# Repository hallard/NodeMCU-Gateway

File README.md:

NodeMCU ESP8266 Gateway Goes to WeMos ESP8266
=============================================

This gateway has been updated by a new version for the following reasons:

- Now I'm using [WeMos D1 Mini][9] board instead of NodeMCU's one because they're just smaller and cheaper (you can find them for less than $3). 
- Features remains the same, they got lot of available shields
- USB Serial onboard is CH340 instead of CP210x, and I can upload up to 900Kbps without any issue on windows 10
- I suspect WeMos regulator far better quality than the one used on NodeMCU that are just fake of original AMS117 3V3.
- Just one size version, no error on order are possible!
- Only one drawback, Voltage input on WeMos is limited to 6V and NodeMCU says up to 20V but trust me, I burnt some at only 14V so If I need to power boards with more than 6V I'm using cheap and small DC/DC converters like this [one][20]one. Plenty on ebay. If you need a more serious and robust one, take this amazing [OKI-78SR-5][21] from Murata (up to 36V).

So for all these reasons I switched to WeMos and created same shields than the ones described here, but, due to size constraint I removed some features, you need to be aware that the following ones has been removed on WeMos shields:

- SPI 2.2" or 1.8" TFT LCD connector
- SPI 128x64 OLED connector (I2C one still present)
- Grove I2C connector (but I2C is exposed via OLED connector)
- Lipo Battery connector
- Data connection for any cheap ebay ASK RX receiver
- **New, a push button** has been added to do some UI/Action if needed.

WeMos Gateway shields are located here: 
- Shield for [RFM69W, RFM69HW, RFM12B or RFM69CW][10] with Atmel ATSHA204 for crypto
- Shield for Lora/LoraWan [RFM92, RFM95, RFM96 or RFM98][11] with footprint for Microchip 24AA02E64 64 bits serial number
- **New Shield** for Lora/LoraWAN [Microchip RN2483][12] with footprint for excellent Microchip RN2483 Lora/Lorawan Module

Sorry there is no shield designed for NRF24L01.

If you need NRF24L01 version or if you just want to continue with the NodeMCU gateway you can, this repo is still alive and boards are working fine.

NodeMCU ESP8266 Gateway
=======================

The gateway can host several funny things like

- Socket to plug a NodeMCU V1.0 (take care 2 version with different width)
- Pins to connect I2C or SPI OLED 128x64
- Pins to connect 2.2" or 1.8" TFT LCD
- RFM69 or RFM12B on board module
- RFM69, RFM12B or NRF24L01 on board module (on NRF version)
- RFM92, RFM95, RFM96, RFM98, RFMH69, RFMHW69 or RFMHCW69 on board module (on LORA version)
- Lipo Battery connector for testing and move the Gateway (no charger on board)
- 3V3 On board regulator is provided by NodeMCU Board
- Data connection for any cheap ebay ASK RX receiver
- One Grove I2C connector to connect other I2C devices
- 2 onboard nice WS2812 RGB LED
- Footprint for Atmel ATSHA204 (I2C version due to lack of I/O)
- Footprint for Microchip 64 bits Unique ID 24AA02E64  (on LORA version)
- Created a version with NRF24L01 connector instead of a grove I2C (end of this page)
- SMA or UFL Antenna connector 

This page has been updated to reflect the GPIO changes and the PCB also, it's now V1.3.

NRF24L01 version are now tested thanks to [mannkind][6]. As suggested NRF version 1.2 has how been corrected to have NRF24L01 wiring same has mysensors configuration and added place for capacitor near NRF24L01.

LORA version have been tested by [lafleur][7] thanks to him.

Take care that on the market you can find lot of NODEMCU boards with different version, and they do not all fit on this. Just because sometime the width of the board if too high. Take care when you order a NodeMCU, see this [post][8]for explanations

New Version 1.3 boards
======================
New boards version V1.3 these boards have some improvments depending on version
- SMA/UFL Antenna connector has been size reduced
- Antenna trace and RF Module surrounded with via for better RF isolation
- Increased "Isolate" ground planes to avoid shorts between connectors and ground (may happen sometimes after soldering)
- I2C OLED connector is now "lock" version, you can just plug to test it will fit without connector
- No more LED solder pad to choose VIN/3V3, added 1N4148 diode from 5V for the 1st LED to decrease VCC to 4.4V, always works
- LORA version, added Microchip 64 bits Unique ID footprint 24AA02E64 
- LORA version, done a diode logic OR for DIO0/DIO1/DIO2 for current LIMC implementation

Version 1.2 boards
==================
New boards version V1.2 these boards add a MOSFET transistor to protect againns reversed power supply. Trust me this will avoid you to burn some nodeMCU board (but nobody plug reversed powed, never ?)

New board, supporing LORA modules

Version 1.1 boards
==================
Boards V1.1 are tested ok (RFM69), no problem at all, just SILK error on TFT connector, TFT pin 4 is RST or VIN (depending on solder pad) not GPIO0, also R3 10K is not needed since GPIO2 is already pulled up by 12K on nodeMCU boards.

SILK problem solved in V1.1a+, I also put VIN/RST solder pad bigger for easier soldering.

This is a bunch of V1.1 white PCB boards, nice ?

Version 1.1 boards
==================
Boards V1.0 worked but I needed a fix for RMF69 pin connection to ESP826 GPIO, let me explain :    
ESP8266 to boot correctly needs some pins at defined level, GPIO15 must be LOW and GPIO2 must be HIGH. Unfortunatlly with RFM69 connected as IRQ to GPIO2 and SS to GPIO15 it does not boot because RF69 pull it DIO IRQ to LOW, making GPIO2 LOW and ESP8266 not booting. The fix is to reverse the wiring, connect IRQ to GPIO15 and SS to GPIO2 (and do according changes in the code).

Detailed Description
====================

No specific documentation for now, but very close in term of feature to Particle Gateway I created and blogged on this dedicated [post][1]

### Schematic (Classic version)

### Boards (Classic version)

You can order the PCB of this board at [OSHPARK][3] (V1.2) or the new V1.3 version at [PCBs.io][13].
PCBs.io give me some reward when you order my designed boards from their site. This is pretty good, because I can use these rewards to create and design new boards and order boards for a discounted price, so if you don't care about PCB manufacturer please use PCBs.io.

### Assembled boards

*V1.0 tested and assembled boards*    

With a nice 1.3" Oled display    

### Schematic (NRF24L01 version)

### Boards (NRF24L01 version)

You can order the PCB of this board at [OSHPARK][4] (V1.2) or the new V1.3 version at [PCBs.io][14].
PCBs.io give me some reward when you order my designed boards from their site. This is pretty good, because I can use these rewards to create and design new boards and order boards for a discounted price, so if you don't care about PCB manufacturer please use PCBs.io.

### Schematic (LORA version)

### Boards (LORA version)

You can order the PCB of this board at [OSHPARK][5] (V1.2) or the new V1.3 version at [PCBs.io][15].
PCBs.io give me some reward when you order my designed boards from their site. This is pretty good, because I can use these rewards to create and design new boards and order boards for a discounted price, so if you don't care about PCB manufacturer please use PCBs.io.

## Bill Of Material

Nothing fancy, all components are 0805 and can be ordered almost anywhere (digikey, mouser, radiospare, ...) 

The tricky one is the RGB LED called "PL9823 F5" can be found on aliexpress or ebay.

## License

You can do whatever you like with this design.

## Misc
See news and other projects on my [blog][2] 
 
[1]: https://hallard.me/particle-gateway/
[2]: https://hallard.me
[3]: https://oshpark.com/shared_projects/vwEm8gUg
[4]: https://oshpark.com/shared_projects/3wE3bYYY
[5]: https://oshpark.com/shared_projects/HIb6K9BL
[6]: https://github.com/hallard/NodeMCU-Gateway/issues/1
[7]: http://forum.thethingsnetwork.org/t/single-channel-gateway/798/147
[8]: http://forum.thethingsnetwork.org/t/single-channel-gateway/798/145
[9]: http://www.wemos.cc/Products/d1_mini.html
[10]: https://github.com/hallard/WeMos-RFM69
[11]: https://github.com/hallard/WeMos-Lora
[12]: https://github.com/hallard/WeMos-RN2483
[13]: https://PCBs.io/share/z7xX4 
[14]: https://PCBs.io/share/z5yGz 
[15]: https://PCBs.io/share/zvJjz 

[20]: http://www.ebay.com/itm/DC-DC-Step-Down-Buck-Power-Supply-5V-28V-to-3-3V-3A-Precise-Fixed-Output-
[21]: http://www.mouser.fr/Search/Refine.aspx?Keyword=OKI-78SR-5

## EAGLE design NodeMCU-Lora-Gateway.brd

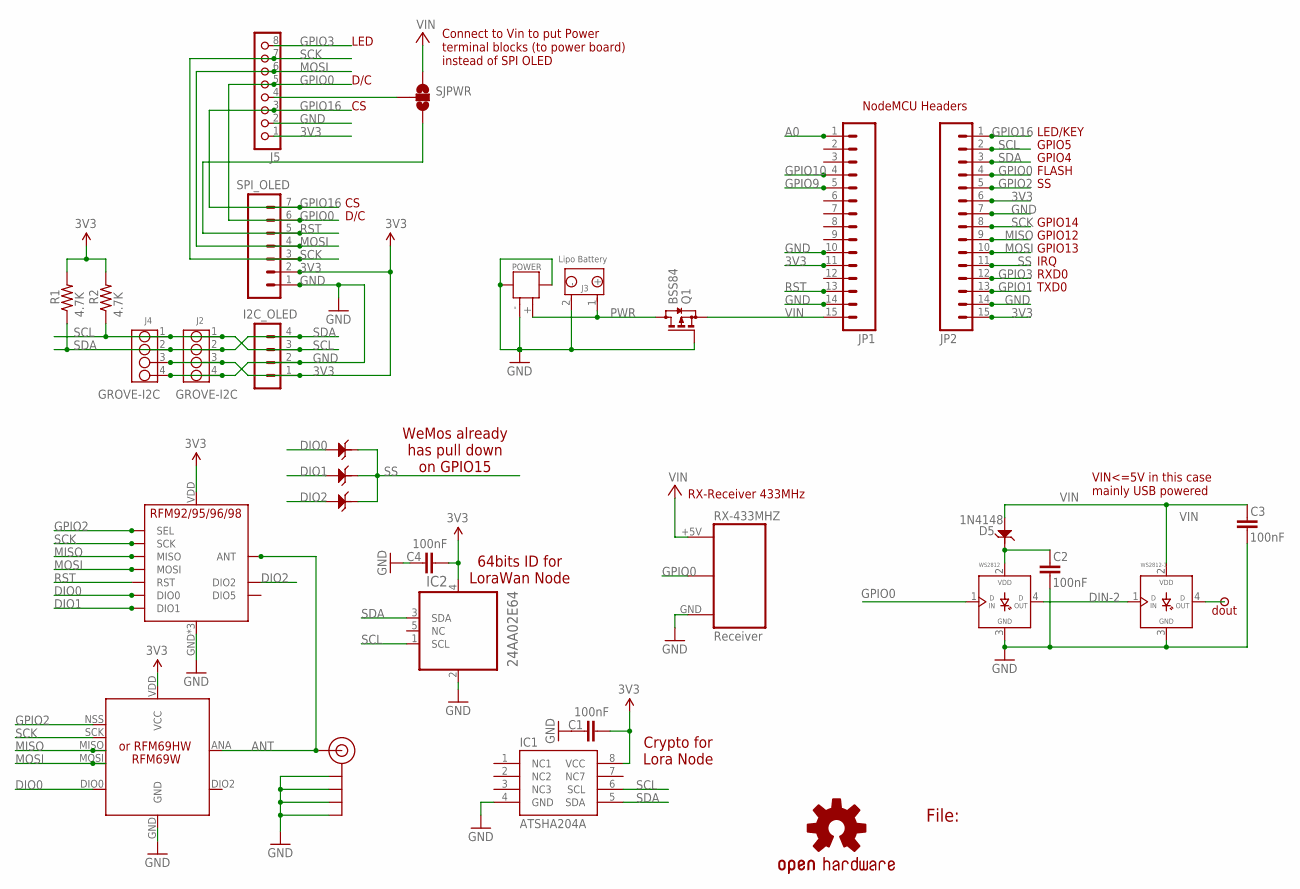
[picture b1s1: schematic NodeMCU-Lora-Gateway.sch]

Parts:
C1, C2, C3, C4: 100nF; 0805-CAP
D0, D1, D2, D5: 1N4148; SOD123-2.7X1.6
I2C_OLED: CON_HEADER_1X04'LOCK'; 1X04_LOCK
IC1: ATSHA204A; SOIC8
IC2: 24AA02E64; SOT95P270X145-5N
J2: GROVE-I2C; 4P-2.0-90D
J3: Lipo Battery; 2P-2.0-90D
J4: GROVE-I2C; 4P-2.0
J5: CON_HEADER_1X08-PTH; M1X8
J$1: ANTENNATINY; SMA_UFL_PAD_TINY
JP1, JP2: M15LOCK; 1X15_LOCK
LOGO2: OSHW-LOGOL; OSHW-LOGO-L
P2: PADNORMAL; PAD
POWER: JST-2P-SMD'2.0'; 2P-SMD-2.0-90D
Q1: BSS84; SOT23
R1, R2: 4.7K; 0805-RES
RX-433MHZ: Receiver; RF-LINK_RX_NO_SILK
SJPWR: JUMPER-PAD-3-2OF3_NC_BY_TRACE_LARGE; PAD-JUMPER-3-2OF3_NC_BY_TRACE_YES_SILK_LARGE
SPI_OLED: CON_HEADER_1X07'SMALL'; M1X7
U1: RFM9x; RFM95
U$3: RFM69W; RFM69W-MINPADS
WS2812, WS2812-1: WS2812B; WS2812-PTH

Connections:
3V3: C1.2, C4.2, I2C_OLED.1, IC1.8 (VCC), IC2.4 (VCC), J2.3, J4.3, J5.1, JP1.11, JP2.6, JP2.15, R1.2, R2.2, SPI_OLED.2, U1.VDD (VCC), U$3.VDD (VCC)
A0: JP1.1
ANT: J$1.ANT1 (SIGNAL), J$1.ANT2 (SIGNAL), J$1.ANT3 (SIGNAL), U1.ANT, U$3.ANA (ANT)
DIN-2: WS2812.4 (DOUT), WS2812-1.1 (DIN)
DIO0: D0.1, U1.DIO0, U$3.DIO0
DIO1: D1.1, U1.DIO1
DIO2: D2.1, U1.DIO2
GND: C1.1, C2.1, C3.1, C4.1, I2C_OLED.2, IC1.4 (GND), IC2.2 (VSS), J2.4, J3.2 (-), J4.4, J5.2, J$1.GND1 (GND), J$1.GND2 (GND), J$1.GND3 (GND), J$1.GND4 (GND), JP1.10, JP1.14, JP2.7, JP2.14, POWER.3, POWER.4, POWER.- (2), Q1.1 (G), RX-433MHZ.GND, SPI_OLED.1, U1.GND, U1.GND1 (GND), U1.GND2 (GND), U$3.GND, WS2812.3 (GND), WS2812-1.3 (GND)
GPIO0: J5.5, JP2.4, RX-433MHZ.DATA@1 (DATA), RX-433MHZ.DATA@2 (DATA), SPI_OLED.6, WS2812.1 (DIN)
GPIO1: JP2.13
GPIO2: JP2.5, U1.NSS (SEL), U$3.NSS (SEL)
GPIO3: J5.8, JP2.12
GPIO9: JP1.5
GPIO10: JP1.4
GPIO16: J5.3, JP2.1, SPI_OLED.7
MISO: JP2.9, U1.MISO, U$3.MISO
MOSI: J5.6, JP2.10, SPI_OLED.4, U1.MOSI, U$3.MOSI
unnamed: P2.1, WS2812-1.4 (DOUT)
unnamed: J5.4, SJPWR.2
PWR: J3.1 (+), POWER.+ (1), Q1.3 (D)
RST: JP1.13, SJPWR.3, SPI_OLED.5, U1.RST
SCK: J5.7, JP2.8, SPI_OLED.3, U1.SCK, U$3.SCK
SCL: I2C_OLED.3, IC1.6 (SCL), IC2.1 (SCL), J2.1, J4.1, JP2.2, R2.1
SDA: I2C_OLED.4, IC1.5 (SDA), IC2.3 (SDA), J2.2, J4.2, JP2.3, R1.1
SS: D0.2, D1.2, D2.2, JP2.11
VIN: C3.2, D5.1, JP1.15, Q1.2 (S), RX-433MHZ.+5V, SJPWR.1, WS2812-1.2 (VDD)
VLED: C2.2, D5.2, WS2812.2 (VDD)

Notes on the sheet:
or RFM69HW
RX-Receiver 433MHz
D/C
LED
File:
FLASH
GPIO12
GPIO4
GPIO5
RXD0
TXD0
GPIO13
GPIO14
IRQ
LED/KEY
NodeMCU Headers
Connect to Vin to put Power terminal blocks (to power board) instead of SPI OLED
VIN<=5V in this case mainly USB powered
dout
64bits ID for LoraWan Node
Crypto for Lora Node
WeMos already has pull down on GPIO15

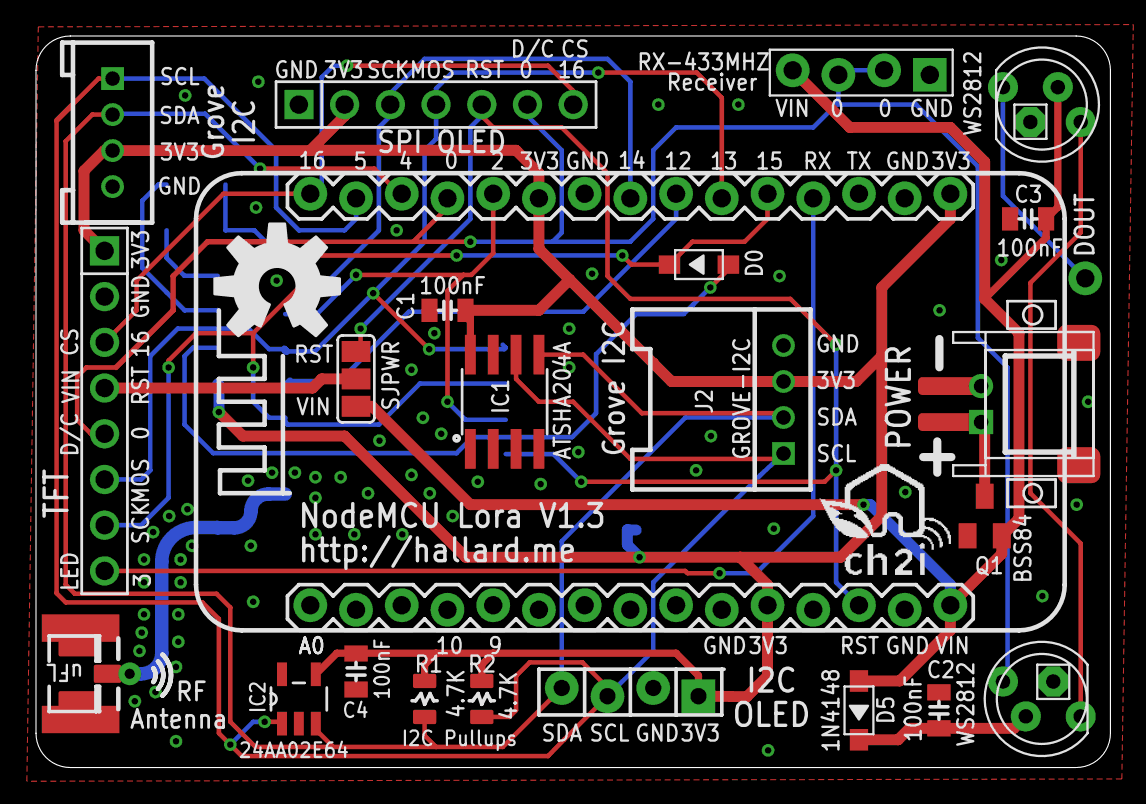
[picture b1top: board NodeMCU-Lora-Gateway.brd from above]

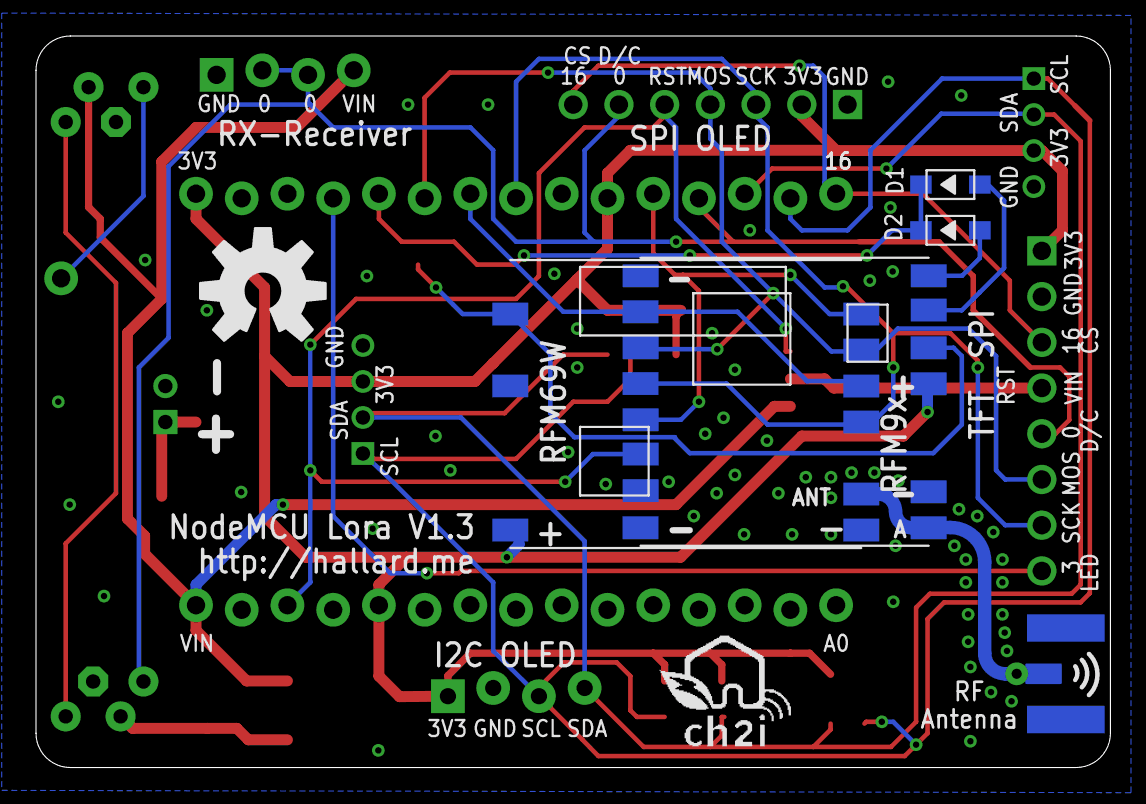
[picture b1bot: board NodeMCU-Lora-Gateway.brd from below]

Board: 2 copper layers, 59.7 x 40.6 mm, 34 parts (6 on the bottom side), 23 nets.

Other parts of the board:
LOGO1: OSHW-LOGOL; OSHW-LOGO-L
U$1, U$4: LOGO_CH2I_75MM

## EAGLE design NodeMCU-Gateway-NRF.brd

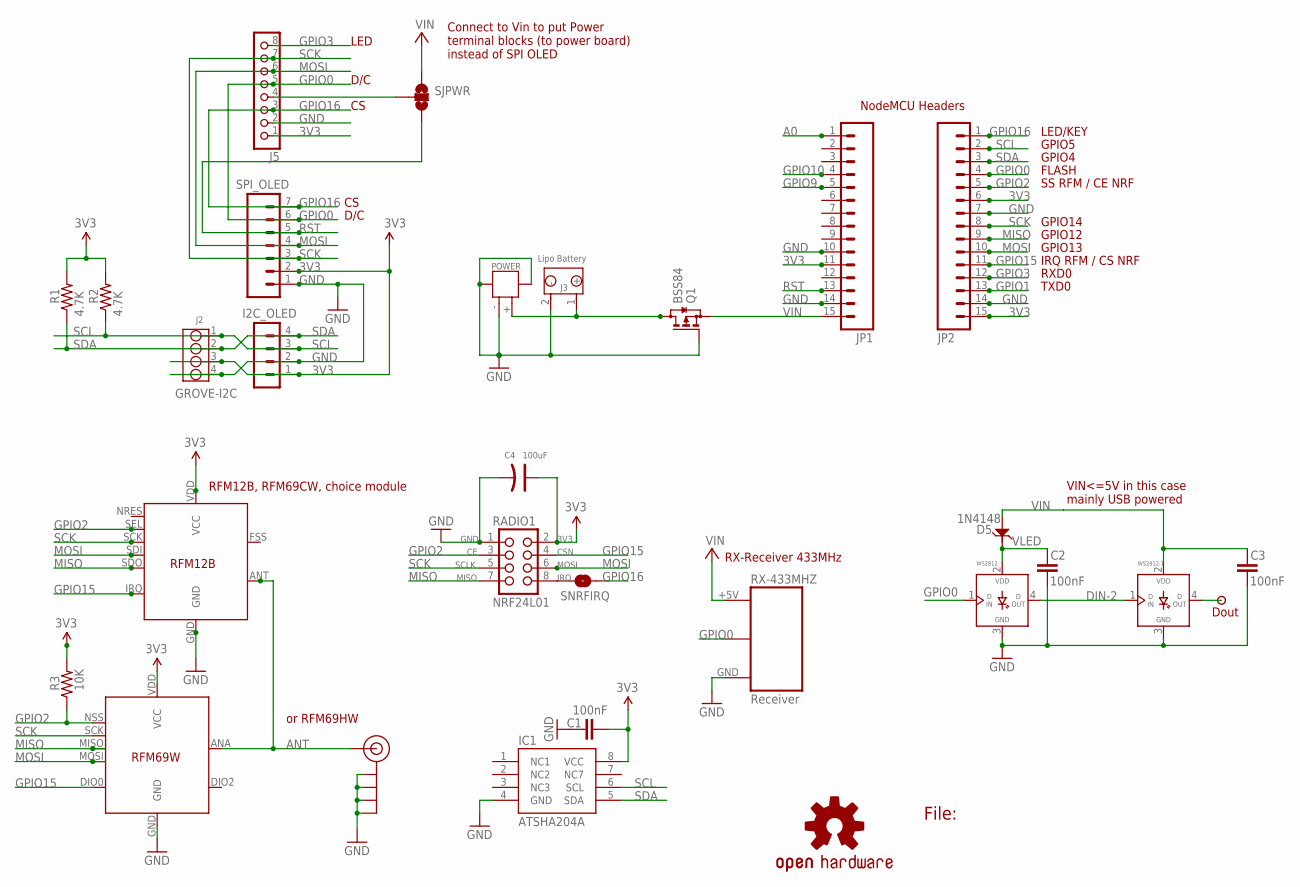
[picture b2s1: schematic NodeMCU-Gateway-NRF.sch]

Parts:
C1, C2, C3: 100nF; 0805-CAP
C4: 100uF; RADIAL-2.0-D5.0*H7MM
D5: 1N4148; SOD123-2.7X1.6
I2C_OLED: CON_HEADER_1X04'LOCK'; 1X04_LOCK
IC1: ATSHA204A; SOIC8
J2: GROVE-I2C; 4P-2.0-90D
J3: Lipo Battery; 2P-2.0-90D
J5: CON_HEADER_1X08-PTH; M1X8
J$2: ANTENNATINY; SMA_UFL_PAD_TINY
JP1, JP2: M15LOCK; 1X15_LOCK
LOGO2: OSHW-LOGOL; OSHW-LOGO-L
P2: PADNORMAL; PAD
POWER: JST-2P-SMD'2.0'; 2P-SMD-2.0-90D
Q1: BSS84; SOT23
R1, R2: 4.7K; 0805-RES
R3: 10K; 0805-RES
RADIO1: NRF24L01; 2X04_NO_LOCK
RX-433MHZ: Receiver; RF-LINK_RX_NO_SILK
SJPWR: JUMPER-PAD-3-2OF3_NC_BY_TRACE_LARGE; PAD-JUMPER-3-2OF3_NC_BY_TRACE_YES_SILK_LARGE
SNRFIRQ: NRFIRQ; PAD-JUMPER-2-NO_YES_SILK
SPI_OLED: CON_HEADER_1X07'SMALL'; M1X7
U$2: RFM12B; RFM12B-MINPADS
U$3: RFM69W; RFM69W-MINPADS
WS2812, WS2812-1: WS2812B; WS2812-PTH

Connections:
3V3: C1.2, C4.+, I2C_OLED.1, IC1.8 (VCC), J2.3, J5.1, JP1.11, JP2.6, JP2.15, R1.2, R2.2, R3.2, RADIO1.2 (3V3), SPI_OLED.2, U$2.VDD (VCC), U$3.VDD (VCC)
A0: JP1.1
ANT: J$2.ANT1 (SIGNAL), J$2.ANT2 (SIGNAL), J$2.ANT3 (SIGNAL), U$2.ANT, U$3.ANA (ANT)
DIN-2: WS2812.4 (DOUT), WS2812-1.1 (DIN)
GND: C1.1, C2.1, C3.1, C4.-, I2C_OLED.2, IC1.4 (GND), J2.4, J3.2 (-), J5.2, J$2.GND1 (GND), J$2.GND2 (GND), J$2.GND3 (GND), J$2.GND4 (GND), JP1.10, JP1.14, JP2.7, JP2.14, POWER.3, POWER.4, POWER.- (2), Q1.1 (G), RADIO1.1 (GND), RX-433MHZ.GND, SPI_OLED.1, U$2.GND, U$3.GND, WS2812.3 (GND), WS2812-1.3 (GND)
GPIO0: J5.5, JP2.4, RX-433MHZ.DATA@1 (DATA), RX-433MHZ.DATA@2 (DATA), SPI_OLED.6, WS2812.1 (DIN)
GPIO1: JP2.13
GPIO2: JP2.5, R3.1, RADIO1.3 (CE), U$2.SEL, U$3.NSS (SEL)
GPIO3: J5.8, JP2.12
GPIO9: JP1.5
GPIO10: JP1.4
GPIO15: JP2.11, RADIO1.4 (CSN), U$2.IRQ, U$3.DIO0
GPIO16: J5.3, JP2.1, SNRFIRQ.2, SPI_OLED.7
MISO: JP2.9, RADIO1.7 (MISO), U$2.SDO, U$3.MISO
MOSI: J5.6, JP2.10, RADIO1.6 (MOSI), SPI_OLED.4, U$2.SDI, U$3.MOSI
unnamed: P2.1, WS2812-1.4 (DOUT)
unnamed: J5.4, SJPWR.2
unnamed: RADIO1.8 (IRQ), SNRFIRQ.1
PWR: J3.1 (+), POWER.+ (1), Q1.3 (D)
RST: JP1.13, SJPWR.3, SPI_OLED.5
SCK: J5.7, JP2.8, RADIO1.5 (CLK), SPI_OLED.3, U$2.SCK, U$3.SCK
SCL: I2C_OLED.3, IC1.6 (SCL), J2.1, JP2.2, R2.1
SDA: I2C_OLED.4, IC1.5 (SDA), J2.2, JP2.3, R1.1
VIN: C3.2, D5.1, JP1.15, Q1.2 (S), RX-433MHZ.+5V, SJPWR.1, WS2812-1.2 (VDD)
VLED: C2.2, D5.2, WS2812.2 (VDD)

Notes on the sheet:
RFM12B, RFM69CW, choice module
or RFM69HW
RX-Receiver 433MHz
D/C
LED
File:
SS RFM / CE NRF
FLASH
GPIO12
GPIO4
GPIO5
RXD0
TXD0
GPIO13
GPIO14
IRQ RFM / CS NRF
LED/KEY
NodeMCU Headers
Connect to Vin to put Power terminal blocks (to power board) instead of SPI OLED
VIN<=5V in this case mainly USB powered
Dout

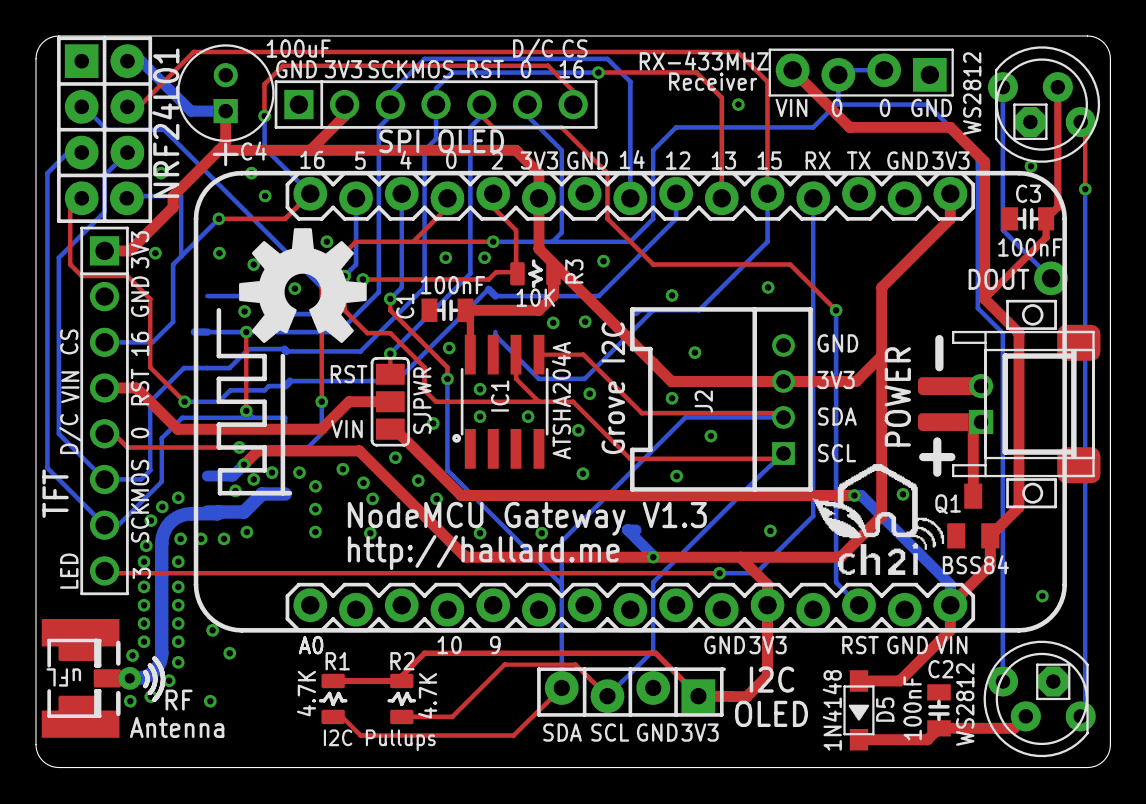
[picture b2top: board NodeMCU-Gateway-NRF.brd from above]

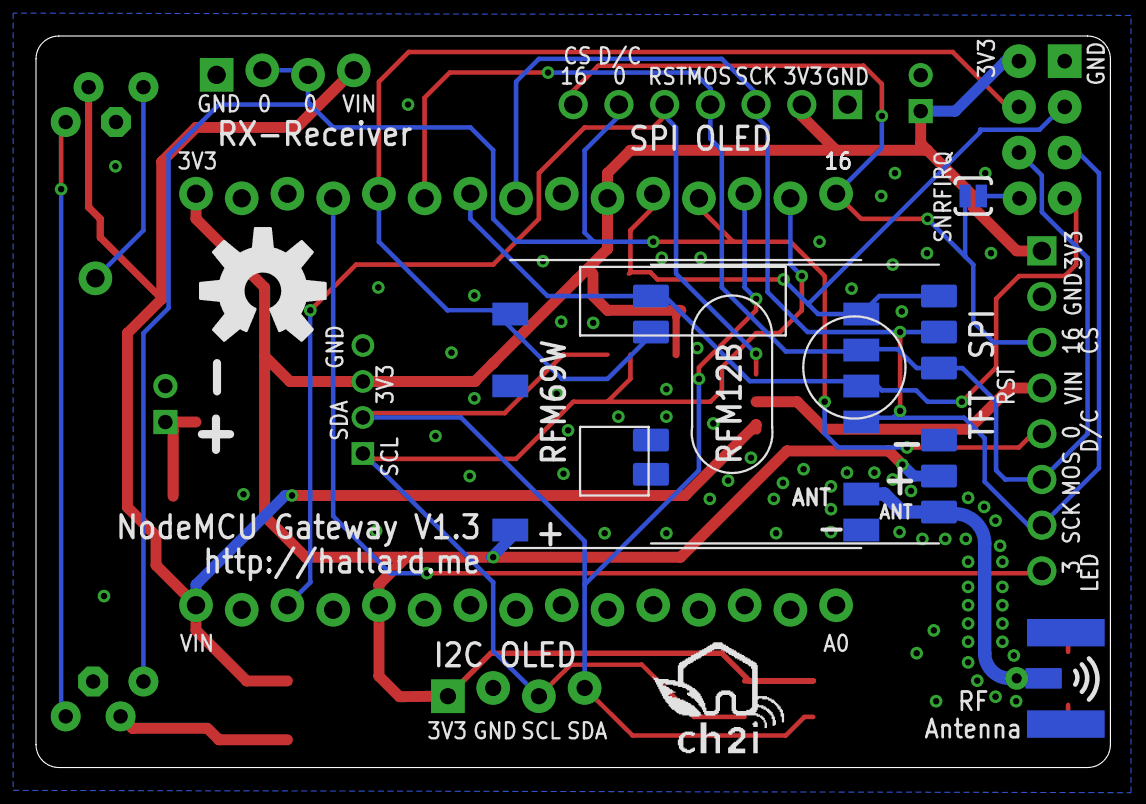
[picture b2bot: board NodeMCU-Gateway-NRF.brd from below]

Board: 2 copper layers, 59.7 x 40.6 mm, 32 parts (5 on the bottom side), 21 nets.

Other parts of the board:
LOGO1: OSHW-LOGOL; OSHW-LOGO-L
U$6, U$7: LOGO_CH2I_75MM

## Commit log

2015-08-28 :confetti_ball: Added .gitattributes
2015-08-28 Creation
2015-08-28 Increased boards image size
2015-10-03 Version 1.1
2015-10-03 Presentation
2015-10-03 Added RGB LED
2015-10-03 Added description on assembled boards
2015-10-04 Added Footprint for ATSHA204
2015-10-04 Added ATSHA204
2015-10-06 Création version NRF24L01
2015-10-06 Added NRF version links
2015-10-06 Added NRF24 schematic version
2015-10-06 Ordered
2015-10-14 Adjust SMA and UFL connectors
2015-10-31 Silk error
    Silk SJPWR is not tied to GPIO0 but RST/VIN
    Increased SJPWR size for easy soldering
2015-10-31 Minor Silk Error
    Silk SJPWR not tied to GPIO0 but RST/VIN
    Increased SJPWR size for easy soldering
2015-10-31 Version 1.1a
2015-10-31 Added White PCB picture
2015-10-31 Picture Link error
2015-11-23 Version 1.1b
    NRF24L01 wiring same as mysensor gateway
    Added place to add cap near NRF24L01
2015-11-23 Version 1.2
    Added FET to protect in case of power reverse, this avoid burning
    NodeMCU board
2015-11-23 Creation
    Direct to V1.2 to conform all other boards and release
2015-11-23 Version 1.2
    Added LORA
2015-11-24 Version 1.2
2015-11-24 deleted new eagle lck files
2015-11-24 Created pictures folder
2016-07-20 Bump to V1.3
    * SMA/UFL Antenna connector has been size reduced
    * Antenna trace and RF Module surrounded with via for better RF
    isolation
    * I2C OLED connector is now "lock" version, you can just plug to test it
    will fit without connector
    * No more LED solder pad to choose VIN/3V3, added 1N4148 diode from 5V
2016-07-20 Bump to V1.3
    * SMA/UFL Antenna connector has been size reduced
    * Antenna trace and RF Module surrounded with via for better RF
    isolation
    * I2C OLED connector is now "lock" version, you can just plug to test it
    will fit without connector
    * Increased "Isolate" ground planes to avoid shorts between connectors
2016-07-20 Bump to V1.3 version
    * SMA/UFL Antenna connector has been size reduced
    * Antenna trace and RF Module surrounded with via for better RF
    isolation
    * Increased "Isolate" ground planes to avoid shorts between connectors
    and ground (may happen sometimes after soldering)
    * I2C OLED connector is now "lock" version, you can just plug to test it
2016-07-20 Cosmetic change
2016-08-03 Added links to WeMos boards
2016-08-03 Typo
2016-08-03 Type
2017-04-18 Fix broken Markdown headings

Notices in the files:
parts and their libraries:
SparkFun-Aesthetics: Licensing: Creative Commons ShareAlike 4.0 International - https://creativecommons.org/licenses/by-sa/4.0
